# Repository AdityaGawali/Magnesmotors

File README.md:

=======
# Smart Battery Charger for Magnes Motors

##### Requirement
1. [ESP-IDF](https://github.com/espressif/esp-idf)

##### Working
ESP_IDF has an excellent support for TCP/UDP sockets but Clients mainly Browsers can only communicate over Websockets.
**Websocets are not TCP sockets.**
Websockets are above the socket layer and are wrapped with  HTTP requests with meta information.

For browsers to communicate over websockets they must establish a *"Handshake"* with the server.
ESP32 acts as psuedo Websocket server which obtains Websocket connection and strips the data and handshakes.

##### Processing
Websocket request looks like this 
```
Host: 192.168.4.1:9998
Connection: Upgrade
Pragma: no-cache
Cache-Control: no-cache
Upgrade: websocket
Origin: file://
Sec-WebSocket-Version: 13
User-Agent: Mozilla/5.0 (Windows NT 6.1; Win64; x64) AppleWebKit/537.36 (KHTML, like Gecko) Chrome/55.0.2883.87 Safari/537.36
Accept-Encoding: gzip, deflate, sdch
Accept-Language: de-DE,de;q=0.8,en-US;q=0.6,en;q=0.4
Sec-WebSocket-Key: Sb0llpkUl572foZxqBOxMw==
Sec-WebSocket-Extensions: permessage-deflate; client_max_window_bits
```
The server has to read Sec-WebSocket-Key, concatinate the  string ```258EAFA5-E914-47DA-95CA-C5AB0DC85B11``` to it, take the SHA1 of it, and return the base64 encoded result to the client For acknowledgement as Handshake.

##### Tasks completed:
1. UART communication with BMS hardware
2. Transmiting the data from UART to CAN 
3. Sending Data to CANBUS  (Testing)
4. Sending Data to Webpage  
5. Merging CAN and WiFi

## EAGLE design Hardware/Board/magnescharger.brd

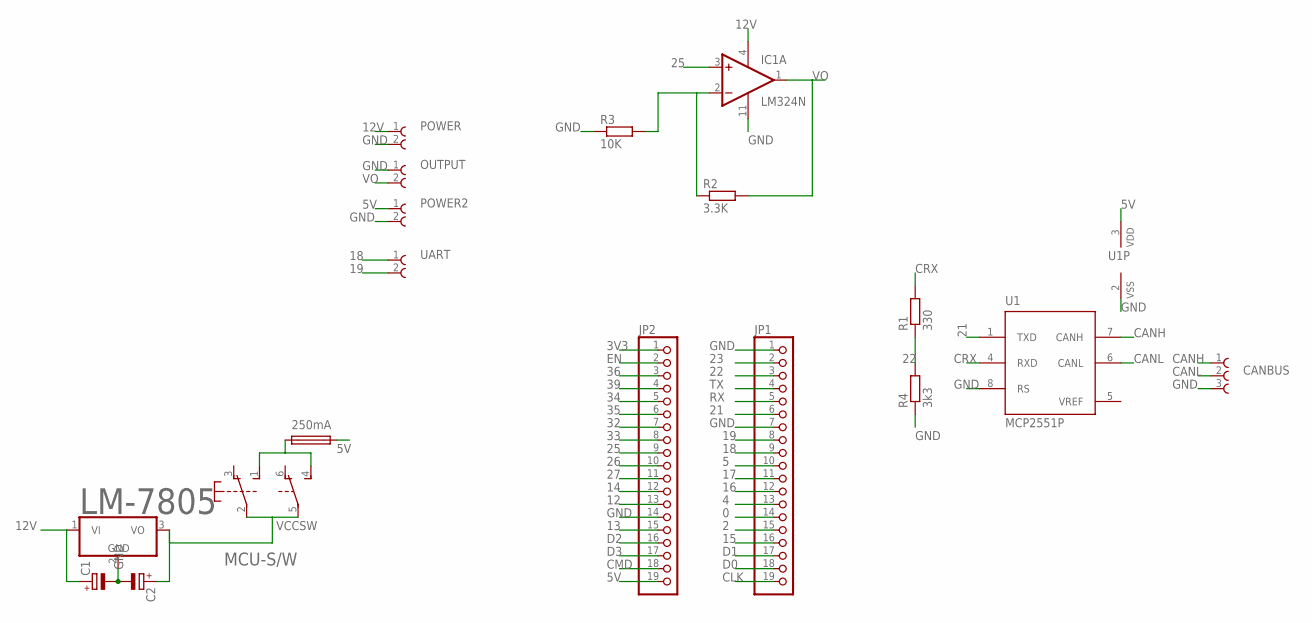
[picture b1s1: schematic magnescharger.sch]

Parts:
C1, C2: CPOL-EUE2.5-6; E2,5-6
CANBUS: 691131710003
F2: 250mA; SH25
IC1: LM324N; DIL14
JP1, JP2: PINHD-1X19; 1X19
LM-7805: 786TV; TO220V
MCU-S/W: 9077-2
OUTPUT: 691131710002
POWER, POWER2: 691131710002
R1: 330; 0207/10
R2: 3.3K; 0207/10
R3: 10K; 0207/10
R4: 3k3; 0207/10
U1: MCP2551P; DIL8
UART: 691131710002

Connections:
0: JP1.14
2: JP1.15
3V3: JP2.1
4: JP1.13
5: JP1.10
5V: F2.2, JP2.19, POWER2.1, U1.3 (VDD)
12: JP2.13
12V: C1.+, IC1.4 (V+), LM-7805.1 (VI), POWER.1
13: JP2.15
14: JP2.12
15: JP1.16
16: JP1.12
17: JP1.11
18: JP1.9, UART.1
19: JP1.8, UART.2
21: JP1.6, U1.1 (TXD)
22: JP1.3, R1.1, R4.2
23: JP1.2
25: IC1.3 (+IN), JP2.9
26: JP2.10
27: JP2.11
32: JP2.7
33: JP2.8
34: JP2.5
35: JP2.6
36: JP2.3
39: JP2.4
CANH: CANBUS.1, U1.7 (CANH)
CANL: CANBUS.2, U1.6 (CANL)
CLK: JP1.19
CMD: JP2.18
CRX: R1.2, U1.4 (RXD)
D0: JP1.18
D1: JP1.17
D2: JP2.16
D3: JP2.17
EN: JP2.2
GND: C1.-, C2.-, CANBUS.3, IC1.11 (V-), JP1.1, JP1.7, JP2.14, LM-7805.2 (GND), OUTPUT.1, POWER.2, POWER2.2, R3.1, R4.1, U1.2 (VSS), U1.8 (RS)
unnamed: F2.1, MCU-S/W.1 (S), MCU-S/W.4 (S)
unnamed: IC1.2 (-IN), R2.1, R3.2
RX: JP1.5
TX: JP1.4
VCCSW: C2.+, LM-7805.3 (VO), MCU-S/W.2, MCU-S/W.5
VO: IC1.1 (OUT), OUTPUT.2, R2.2
VREF: U1.5 (VREF)

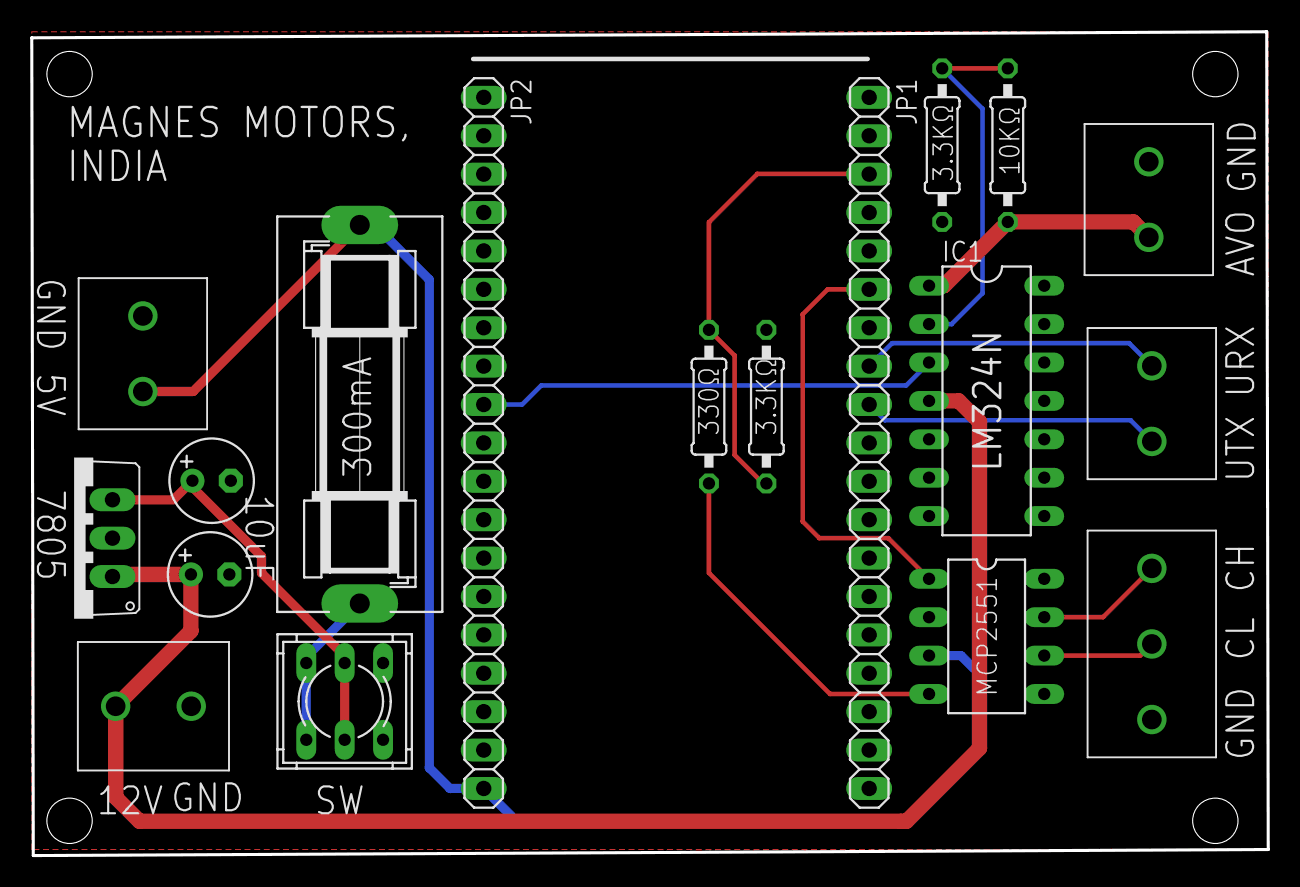
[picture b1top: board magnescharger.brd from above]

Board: 2 copper layers, 81.8 x 54.5 mm, 18 parts (0 on the bottom side), 15 nets.

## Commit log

2019-04-15 magnes IDF
2019-04-15 update repo
2019-04-15 ignore build
2019-04-19 Board resetting issue resolved modified: rs232/main/main.c new file: rs232_to_uart/main/main.c
2019-06-24 update working codes
2019-06-26 CAN and UART update
2019-06-26 README.md update
2019-06-28 Update PCB files
2019-07-01 added CAN communication for charger
2019-07-04 changed feedback resistor value
2019-07-04 cleared error in README.md track
2019-07-07 added mounting holes
2019-07-08 dac_test
2019-07-08 wifi code updated
2019-07-10 modify code
2019-07-11 flashed code update
2019-07-12 final test
2019-07-13 final code changes
2019-07-14 WiFi Manager added
2019-07-15 blocking CANBUS bugs removed
2019-07-22 add status led
2019-07-22 add charger test
2019-07-22 status led added & gitignore not working
2019-07-23 PCB modified
2019-07-23 status active low led

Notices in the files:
parts and their libraries:
Wurth_Elektronik_Electromechanic_Termina: Copyright: Würth Elektronik
